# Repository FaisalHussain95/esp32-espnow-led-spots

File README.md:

# DIY Smart LED Spot Replacement

Replacing 13 cheap 220V ceiling spots with custom COB LED units — dimmable, Home Assistant integrated, actively cooled, and wirelessly controlled over ESP-NOW.

```mermaid
graph LR
    HA[🏠 Home Assistant]

    subgraph wifi_net[IoT WiFi network]
        BR[WiFi Bridge\nESP32-C3 SuperMini\nWiFi mode]
    end

    subgraph espnow_net[ESP-NOW ch11 — AES-128 — no WiFi]
        MA[Master\nESP32-C3 SuperMini]
        S1[Spot 1\nESP32-C3]
        S2[Spot 2\nESP32-C3]
        SN[Spot 3…13\nESP32-C3]
        MA <-->|ESP-NOW| S1
        MA <-->|ESP-NOW| S2
        MA <-->|ESP-NOW| SN
    end

    HA <-->|MQTT| BR
    BR <-->|UART 115200| MA
```

---

## The problem

I have 13 recessed spots installed across my ceiling. They were cheap 220V AC units with no heatsink — just a bare aluminium PCB glued to a plastic shell.

Opening one up tells the whole story: the driver circuit runs directly off mains voltage with no thermal management whatsoever.

After about 5000 hours one by one they started dying from overheating. Rather than buying the same thing again, I decided to rebuild them properly.

---

## The goals

- **Reuse the existing shells** — no new ceiling holes
- **Use COB LEDs from stock** — 5W COB with a proper heatsink and active cooling to make them last
- **Dimmable** — the original spots were on/off only
- **Home Assistant integration** — via MQTT
- **OTA updates** — to add effects or fix bugs without a ladder (we already added a pulse effect and smooth fade in/out)
- **No per-spot WiFi** — 13 devices on the IoT network is too much; ESP-NOW keeps them off WiFi entirely

---

## Why not a simpler controller?

The ESP32 is overkill for dimming a light, I know. The constraint was the existing wiring in the ceiling: when it was first installed nobody thought about future upgrades, so we are stuck with the cables already there. Running a new PWM signal cable through the ceiling was not feasible. We needed a device that could receive wireless commands and that I already knew how to program — hence ESP32 + ESP-NOW.

---

## Power: from 220V mains to 24V DC

The original spots each had their own mains driver. The replacement approach uses a single shared 24V DC rail for all spots.

**Power supply: TRACO TSP 180-124 — 24V / 180W**

The supply sits centrally, with two cable runs of 15m each covering all spots.

### Cable sizing

Existing cable: 2.5mm² solid copper (13 AWG), already in the ceiling (previously carrying 220V).

- COB LED: ~7W max, running at PWM 160/255 → ~4.4W effective
- ESP32-C3: ~0.5W
- Budget per spot: **~12W to be safe** → total load: 13 × 12W = **156W / 24V = 6.5A** across the full 30m run
- Per 15m path: **max ~3A**

Using a [wire size calculator](https://www.omnicalculator.com/physics/wire-size) with 3A over 15m and a 10% voltage drop tolerance, 2.5mm² is sufficient. The cable was already there — we just repurposed it from 220V AC to 24V DC.

---

## The replacement unit

Each spot gets a self-contained module: COB LED + heatsink + fan + NTC + ESP32-C3 + custom PCB.

### COB LED on heatsink

### With fan mounted

The 25×25mm fan sits on top of the heatsink. It is 5V PWM-controlled, kicks in above 45°C and cuts off below 40°C. At normal brightness the fan rarely runs.

### NTC thermal protection

An MF52 10kΩ NTC is mounted against the heatsink. The firmware reads it every second and applies progressive PWM throttling at 60°C, a hard floor at 75°C, and alerts the master controller at 85°C.

---

## The PCB

The driver electronics sit on a custom KiCad board that fits inside the spot shell. It carries the MP1584 buck converter (24V → 3.3V), PT4115 LED driver, fan MOSFET, NTC input, and the ESP32-C3 SuperMini.

**Manufacturing files for JLCPCB** (Gerbers, BOM, CPL) are in [kicad/diy_led_spot/v4/](kicad/diy_led_spot/v4/). The KiCad project itself is in [kicad/diy_led_spot/](kicad/diy_led_spot/).

---

## How it works

Each spot is an ESP32-C3 node. An ESP32-C3 SuperMini acts as master. A second ESP32-C3 SuperMini bridges MQTT to the master over UART. The spots never touch WiFi during normal operation — everything runs over ESP-NOW on a dedicated channel.

```mermaid
sequenceDiagram
    participant HA as Home Assistant
    participant BR as WiFi Bridge<br/>(ESP32-C3 SuperMini)
    participant MA as Master<br/>(ESP32-C3 SuperMini)
    participant SP as Spot × N<br/>(ESP32-C3)
    participant GH as GitHub Releases<br/>(OTA)

    note over SP,MA: ── Boot handshake (ESP-NOW ch11, AES-128) ──
    SP->>MA: MSG_HELLO {spot_id, fw_version}
    alt version OK
        MA->>SP: MSG_ACK
    else version outdated
        MA->>SP: MSG_REJECT + MSG_OTA_NOW {target_version}
        SP->>GH: HTTP GET slave_c3_supermini_vN.bin
        GH-->>SP: firmware binary → flash & reboot
    end

    note over MA: Master reboot → rediscover all spots
    MA->>SP: MSG_WHOIS (broadcast)
    SP->>MA: MSG_HELLO (re-announce)

    note over HA,SP: ── Normal operation ──
    HA->>BR: MQTT homeassistant/led_spots/{id}/set<br/>{"state":"ON","brightness":200}
    BR->>MA: UART frame 0xAA 0x01 spot_id bri cmd 0x55
    MA->>SP: MSG_CMD {spot_id, CMD_TURN_ON, brightness}

    SP-->>MA: MSG_STATUS every 10 s<br/>{spot_id, brightness, temp°C, thermal_state, is_on}
    MA-->>BR: UART frame 0xAA 0x02 spot_id bri temp_hi temp_lo thermal 0x55
    BR-->>HA: MQTT homeassistant/led_spots/{id}/state<br/>{"state":"ON","brightness":200,"temperature":42.3}

    note over SP: ── Thermal protection (on-spot) ──
    SP->>SP: NTC read every 1 s<br/>60°C → throttle PWM<br/>85°C → PWM floor + alert
    SP-->>MA: MSG_STATUS {thermal_state: critical}

    note over HA,GH: ── OTA triggered from HA ──
    HA->>BR: MQTT homeassistant/led_spots/ota/set {"version":30}
    BR->>MA: UART frame 0xAA 0x03 target_version 0x55
    MA->>SP: MSG_OTA_NOW {target_version} (broadcast)
    SP->>GH: HTTP GET slave_c3_supermini_v30.bin
    GH-->>SP: firmware binary → flash & reboot
```

For the full technical details, wiring, firmware architecture, and PCB design see [TECHNICAL.md](TECHNICAL.md).

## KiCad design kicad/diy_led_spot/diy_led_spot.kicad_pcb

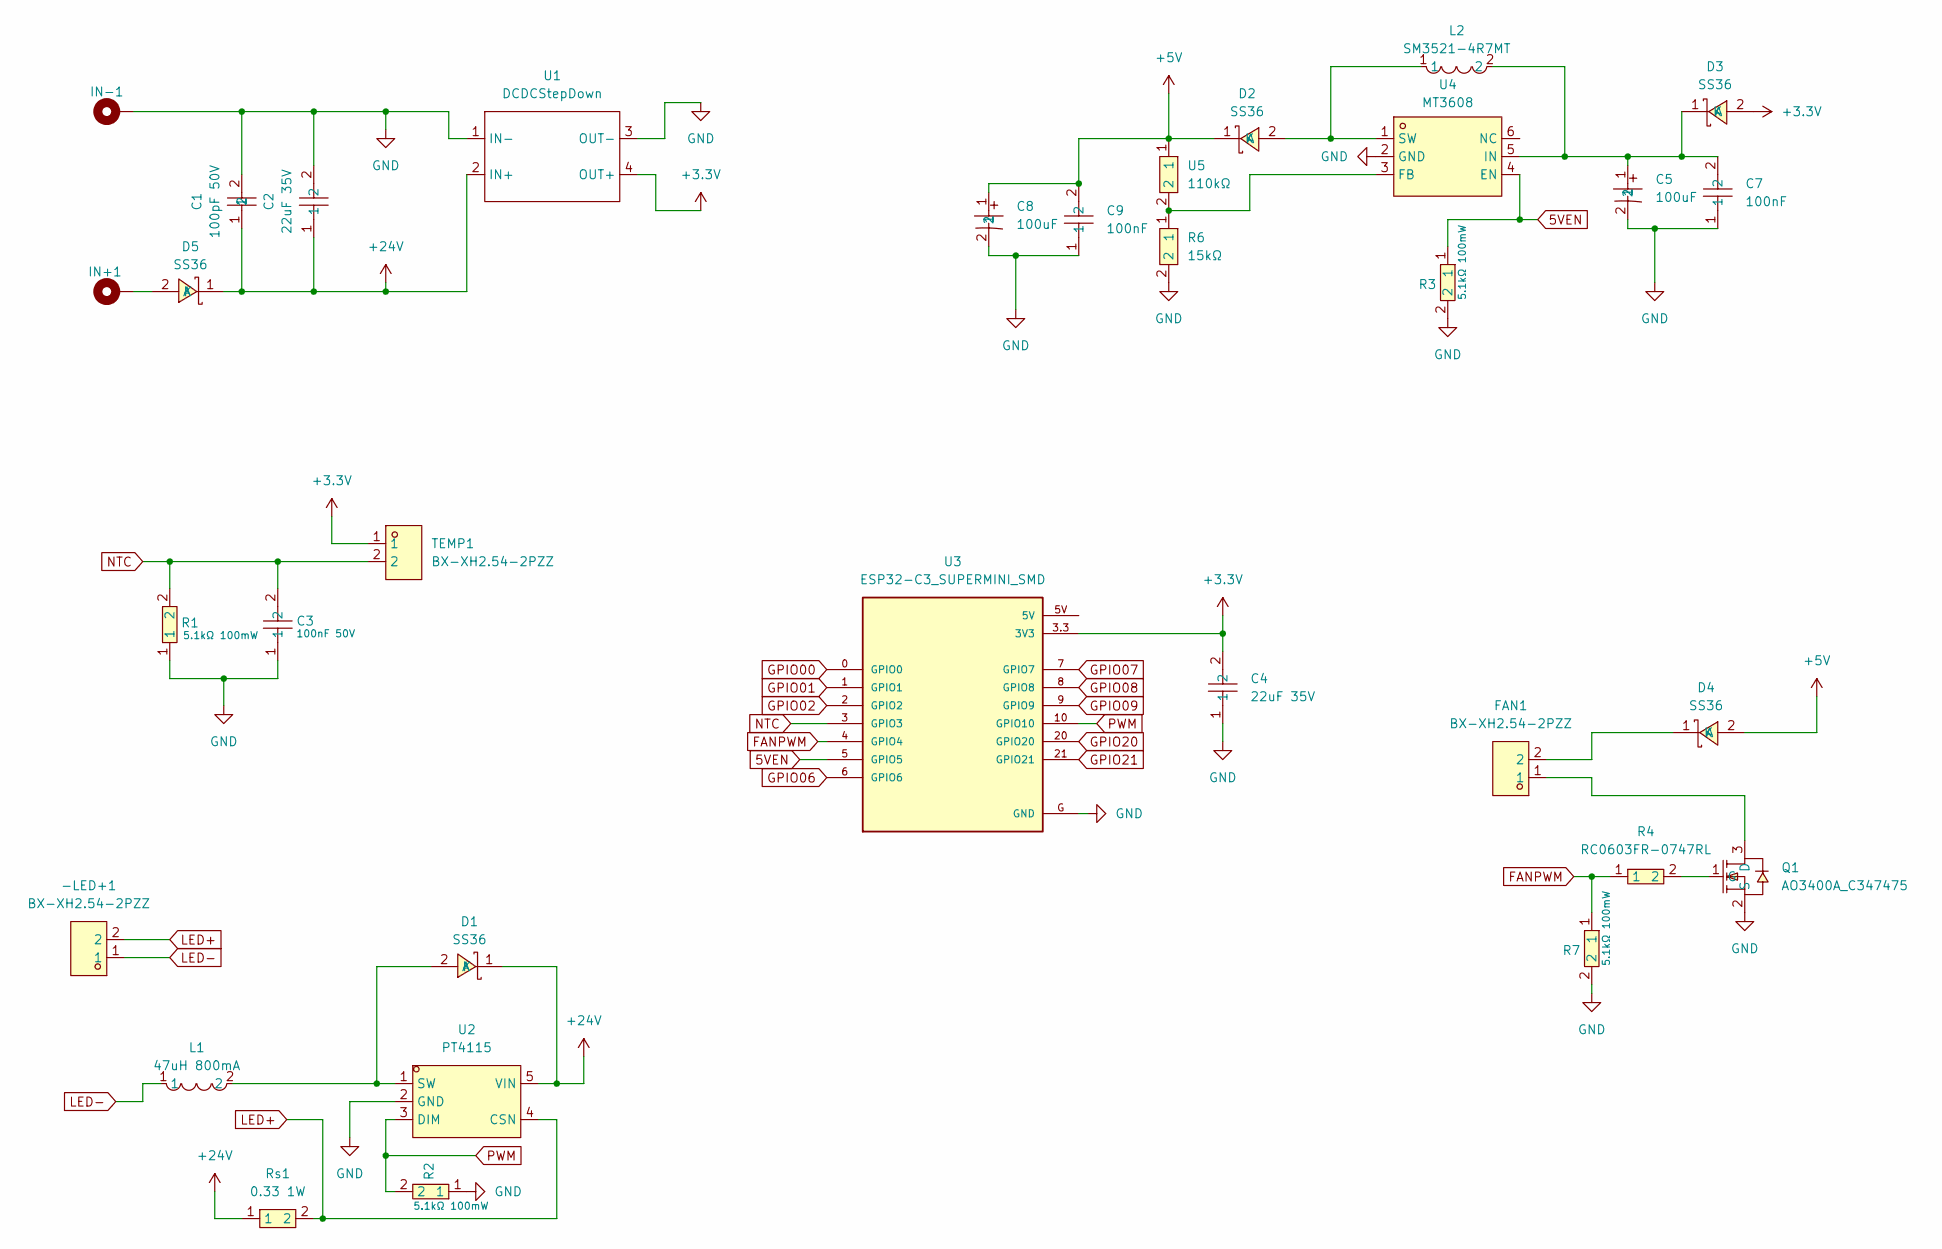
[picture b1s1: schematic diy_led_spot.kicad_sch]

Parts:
-LED+1: BX-XH2.54-2PZZ; CONN-TH_2P-P2.50_BX-XH2.54-2PZZ; LCSC Part C18077833
C1: 100pF 50V; C0603; LCSC Part C14858
C2, C4: 22uF 35V; C0805; LCSC Part C6119901
C3: 100nF 50V; C0805; LCSC Part C476766
C5, C8: 100uF; CAP-SMD_BD5.0-L5.3-W5.3-LS6.3-FD; LCSC Part C72473
C7, C9: 100nF; C0402; LCSC Part C307331
D1, D2, D3, D4, D5: SS36; SMA_L4.3-W2.6-LS5.2-RD; LCSC Part C16015
FAN1: BX-XH2.54-2PZZ; CONN-TH_2P-P2.50_BX-XH2.54-2PZZ; LCSC Part C18077833
IN+1: MountingHole_Pad; MountingHole_2.2mm_M2_DIN965_Pad_TopBottom
IN-1: MountingHole_Pad; MountingHole_2.2mm_M2_DIN965_Pad_TopBottom
L1: 47uH 800mA; IND-SMD_L4.0-W4.0_FNR40XXS; LCSC Part C167888
L2: SM3521-4R7MT; IND-SMD_L3.5-W3.0; LCSC Part C35602
Q1: AO3400A_C347475; SOT-23-3_L2.9-W1.3-P1.90-LS2.4-BR; LCSC Part C347475
R1, R2, R3, R7: 5.1kΩ 100mW; R0603; LCSC Part C23186
R4: RC0603FR-0747RL; R0603; LCSC Part C114623
R6: 15kΩ; R0603; LCSC Part C2906995
Rs1: 0.33 1W; R2512; LCSC Part C19269965
TEMP1: BX-XH2.54-2PZZ; CONN-TH_2P-P2.50_BX-XH2.54-2PZZ; LCSC Part C18077833
U1: DCDCStepDown; DCDCBuck5V-30V_To_3.3V_5V_9V_12V_3A
U2: PT4115; SOT-89-5_L4.5-W2.5-P1.50-LS4.5-BR; LCSC Part C347356
U3: ESP32-C3_SUPERMINI_SMD; MODULE_ESP32-C3_SUPERMINI
U4: MT3608; SOT-23-6_L2.9-W1.6-P0.95-LS2.8-BL; LCSC Part C84817
U5: 110kΩ; R0603; LCSC Part C2906984

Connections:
5VEN: R3.1, U3.5 (GPIO5), U4.4 (EN)
+3.3V: C4.2, D3.2 (A), TEMP1.1, U1.4 (OUT+), U3.3.3 (3V3)
+5V: C8.1, C9.2, D2.1 (K), D4.2 (A), U5.1
+24V: C1.1, C2.1, D1.1 (K), D5.1 (K), Rs1.1, U1.2 (IN+), U2.5 (VIN)
FANPWM: R4.1, R7.1, U3.4 (GPIO4)
GND: C1.2, C2.2, C3.1, C4.1, C5.2, C7.1, C8.2, C9.1, IN-1.1, Q1.2 (S), R1.1, R2.1, R3.2, R6.2, R7.2, U1.1 (IN-), U1.3 (OUT-), U2.2 (GND), U3.G (GND), U4.2 (GND)
GPIO00: U3.0 (GPIO0)
GPIO01: U3.1 (GPIO1)
GPIO02: U3.2 (GPIO2)
GPIO06: U3.6 (GPIO6)
GPIO07: U3.7 (GPIO7)
GPIO08: U3.8 (GPIO8)
GPIO09: U3.9 (GPIO9)
GPIO20: U3.20 (GPIO20)
GPIO21: U3.21 (GPIO21)
LED+: -LED+1.2, Rs1.2, U2.4 (CSN)
LED-: -LED+1.1, L1.1
NTC: C3.2, R1.2, TEMP1.2, U3.3 (GPIO3)
unnamed: D1.2 (A), L1.2, U2.1 (SW)
unnamed: D2.2 (A), L2.1, U4.1 (SW)
unnamed: C5.1, C7.2, D3.1 (K), L2.2, U4.5 (IN)
unnamed: D4.1 (K), FAN1.2
unnamed: D5.2 (A), IN+1.1
unnamed: FAN1.1, Q1.3 (D)
unnamed: Q1.1 (G), R4.2
unnamed: R6.1, U4.3 (FB), U5.2
PWM: R2.2, U2.3 (DIM), U3.10 (GPIO10)

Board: 2 copper layers, 33 parts (0 on the bottom side), 18 nets, no tracks yet.

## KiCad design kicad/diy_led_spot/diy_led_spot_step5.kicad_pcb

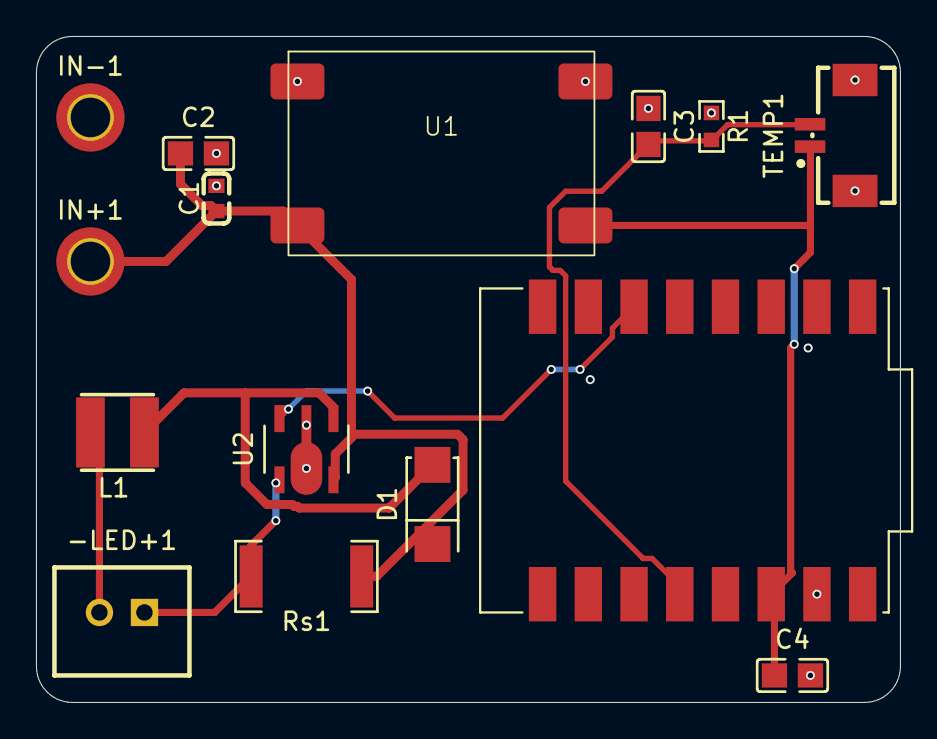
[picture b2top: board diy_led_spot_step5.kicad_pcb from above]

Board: 2 copper layers, 48.0 x 37.0 mm, 15 parts (0 on the bottom side), 8 nets.

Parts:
-LED+1: BX-XH2.54-2PZZ; CONN-TH_2P-P2.50_BX-XH2.54-2PZZ
C1: 100pF 50V; C0603
C2, C4: 22uF 35V; C0805
C3: 100nF 50V; C0805
D1: SS36; SMA_L4.3-W2.6-LS5.2-RD
IN+1: MountingHole_Pad; MountingHole_2.2mm_M2_DIN965_Pad_TopBottom
IN-1: MountingHole_Pad; MountingHole_2.2mm_M2_DIN965_Pad_TopBottom
L1: 47uH 800mA; IND-SMD_L4.0-W4.0_FNR40XXS
R1: 5.1kΩ 100mW; R0603
Rs1: 0.33 1W; R2512
TEMP1: MX1.25-2P; CONN-SMD_2P-P1.25_XUNPU_WAFER-MX1.25-2PWB
U1: DCDCStepDown; DCDCBuck5V-30V_To_3.3V_5V_9V_12V_3A
U2: PT4115; SOT-89-5_L4.5-W2.5-P1.50-LS4.5-BR
U3: ESP32-C3_SUPERMINI_SMD; MODULE_ESP32-C3_SUPERMINI

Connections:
+3.3V: C4.2, TEMP1.1, U1.4 (OUT+), U3.3.3 (3V3)
+24V: C1.1, C2.1, D1.1 (K), IN+1.1, Rs1.1, U1.2 (IN+), U2.5 (VIN)
GND: C1.2, C2.2, C3.1, C4.1, IN-1.1, R1.1, TEMP1.3, TEMP1.4, U1.1 (IN-), U1.3 (OUT-), U2.2 (GND), U3.G (GND)
NTC: C3.2, R1.2, TEMP1.2, U3.3 (GPIO3)
unnamed: -LED+1.2, L1.1
unnamed: D1.2 (A), L1.2, U2.1 (SW)
unnamed: -LED+1.1, Rs1.2, U2.4 (CSN)
PWM: U2.3 (DIM), U3.10 (GPIO10)

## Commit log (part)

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2026-03-01 Init
2026-03-01 perfectly working state
2026-03-04 docs: switch to ESP32-C3 SuperMini + PT4115 CC driver at 24V
    - Replace ESP32-S2-MINI-1-N4 with ESP32-C3 SuperMini as final target MCU
    - Replace IRLZ44N MOSFET with PT4115 constant-current buck driver (Rsense=0.33Ω → 303mA)
    - Switch supply from HLK-PM15 (15V) to HLK-PM24 (24V)
    - Update GPIO assignments: PWM→GPIO10, NTC ADC→GPIO3, status LED→GPIO8 (active LOW)
    - Invert status LED logic in firmware via STATUS_LED_ON/OFF macros
    - Update platformio.ini board to esp32-c3-devkitm-1
2026-03-04 feat: Add KiCad project files for DIY LED Spot project
    - Created diy_led_spot_step5.kicad_prl with board settings, visibility options, and selection filters.
    - Created diy_led_spot_step5.kicad_pro with detailed design settings, net settings, and IPC2581 configurations.
2026-03-04 feat: Implement ESP-NOW OTA system with encryption and provisioning
    - Added OTA functionality to espnow_manager, allowing slaves to receive firmware updates.
    - Introduced provisioning module to handle PMK and WiFi credentials storage in NVS.
    - Updated espnow_manager to support encrypted communication using PMK.
    - Enhanced main firmware logic to trigger OTA updates and handle commands.
    - Created GitHub Actions workflow for automated builds and releases on version tags.
    - Added WiFi bridge firmware to facilitate communication between Home Assistant and LED spots.
2026-03-14 feat: PID thermal, PWM_MAX cap, MSG_WHOIS; firmware OTA + provisioning + PID
    - README: rewrite thermal section to reflect PID controller (Kp=8, Ki=0.5, Kd=5),
    add PWM_MAX=100 hardware ceiling table, add MSG_WHOIS 0x06 to message types table
    - Spot firmware: OTA (HTTP from GitHub releases, 5-retry), provisioning (PMK + WiFi
    creds + spot ID from build_flags → NVS), PID thermal throttle, MSG_WHOIS support
    - Master firmware: UART2 bridge to WiFi ESP32-B, MSG_WHOIS broadcast on boot,
    dynamic peer registration, required fw version + OTA trigger via serial/UART2
2026-03-14 feat(ci): Env names
2026-03-14 chores(ci): Bump action version
2026-03-14 feat: Implement self-OTA functionality for master and bridge firmware with WiFi credential management
2026-03-14 feat: Add environment configuration and credential injection script
2026-03-14 feat: Update firmware version to 2 across all configurations
2026-03-14 feat: Fix OTA functionality
2026-03-14 feat: Update firmware version to 3 across all configurations
2026-03-14 feat: Enhance provisioning and ESPNOW error logging with PMK output
2026-03-14 feat: Update firmware version to 4 across all configurations
2026-03-14 feat: Improve OTA update process with retry mechanism and enhanced error handling
2026-03-14 feat: Update firmware version to 5 across all configurations
2026-03-14 feat: Enhance OTA process with improved WiFi connection handling and ESP-NOW reinitialization
2026-03-14 feat: enhance OTA process with Cloudflare DNS configuration and improve updates
2026-03-14 fix: OTA reliability, ESP-NOW broadcast HELLO, UART2 handshake notify
2026-03-14 feat: Update firmware version to 8 across all configurations
2026-03-14 feat: Fix build
2026-03-14 fix: remove NVS fw_version, add safety LED cutoff on master loss, bump to v9
    - Remove NVS-based _required_fw_version — use compile-time FW_VERSION
    directly, eliminating version desync after failed OTA
    - Spot: track consecutive ESP-NOW send failures, cut LED off after 5
    failures (safety: no uncontrolled LED operation without master)
    - Reset failure counter on successful send or any received packet
2026-03-15 fix: reduce TX power to 10dBm for standalone 3.3V stability, bump to v17
    - Set esp_wifi_set_max_tx_power(40) to reduce TX current spikes that
    may cause voltage sag on standalone MP1584 3.3V supply
    - Print actual TX power on boot for debug
2026-03-21 kicad: save current PCB/schematic state including routed and step3 variants
2026-03-22 kicad: save current PCB/schematic state
2026-03-22 feat: add local serial command parser for bench testing without master
    Adds processSerialCommands() to the spot loop so the LED can be
    controlled directly from the serial monitor (on/off/dim/pulse/status)
    without needing an ESP-NOW master — useful for validating each PCB.
    Also updates COM port to COM9.
2026-03-31 feat: add active fan cooling support (MT3608 + AO3400)
    - GPIO5 enables MT3608 boost (3.3V → 5V) with 2ms startup delay
    - GPIO4 drives AO3400 MOSFET to switch fan ground
    - Fan ON ≥ 50°C, OFF ≤ 45°C (hysteresis), forced ON on NTC fault
    - Update CLAUDE.md with full 3-node architecture and new modules
    - Mark active cooling as done in README next steps
2026-03-31 feat: add PROV serial command for single-flash provisioning
2026-03-31 feat: add PROV serial command + fan cooling, bump to v24
2026-04-04 feat: update PWM limits and fan control temperatures, set default boot state to ON
2026-04-04 feat: Update firmware version to 25 across all configurations
2026-04-04 feat: reduce stabilisation delay in setup for production environment
2026-04-04 feat: update firmware version to 26 across all configurations
2026-04-05 feat: migrate ESP-NOW to channel 11, add wifi scanner, bump to v27
    - Move all ESP-NOW traffic from CH1 to CH11 (cleaner channel in local environment)
    - ESPNOW_CHANNEL define added to both config.h files — single place to change
    - Add wifi_scanner_firmware: standalone TTGO LoRa32 tool that displays per-channel
    AP count as a bar chart on the OLED and streams RSSI table to serial
    - Bump FW_VERSION 26 → 27 across all three firmwares so bridge-master procedure
    can trigger OTA on any spot still running v26/CH1
2026-04-05 feat: streamline WiFi channel scan output, remove unused functions and improve readability
2026-04-05 feat: implement fade-in effect on boot for smoother light activation
2026-04-05 feat: update firmware version to 28 across all configurations
2026-05-01 feat: enhance documentation and improve spots discoverability
2026-05-01 #1 Better describe the project
2026-05-01 feat: add detailed sequence diagram for ESP32 spot communication and OTA process
2026-05-01 feat: add mermaid diagram for ESP32 spot communication architecture
2026-05-01 feat: subgraphs for WiFi and ESP-NOW networks
2026-05-02 NEW Master MAC
2026-05-02 feat: Delete hardcoded master mac
2026-05-02 Migrate to c3 supermini
2026-05-02 feat: Make the master screen optional
2026-05-02 feat: Update firmware version to 30 and refactor master MAC handling
2026-05-02 feat: Set maximum TX power to reduce heat on C3 SuperMini
2026-05-03 chores
2026-05-03 chores: bump to v31
